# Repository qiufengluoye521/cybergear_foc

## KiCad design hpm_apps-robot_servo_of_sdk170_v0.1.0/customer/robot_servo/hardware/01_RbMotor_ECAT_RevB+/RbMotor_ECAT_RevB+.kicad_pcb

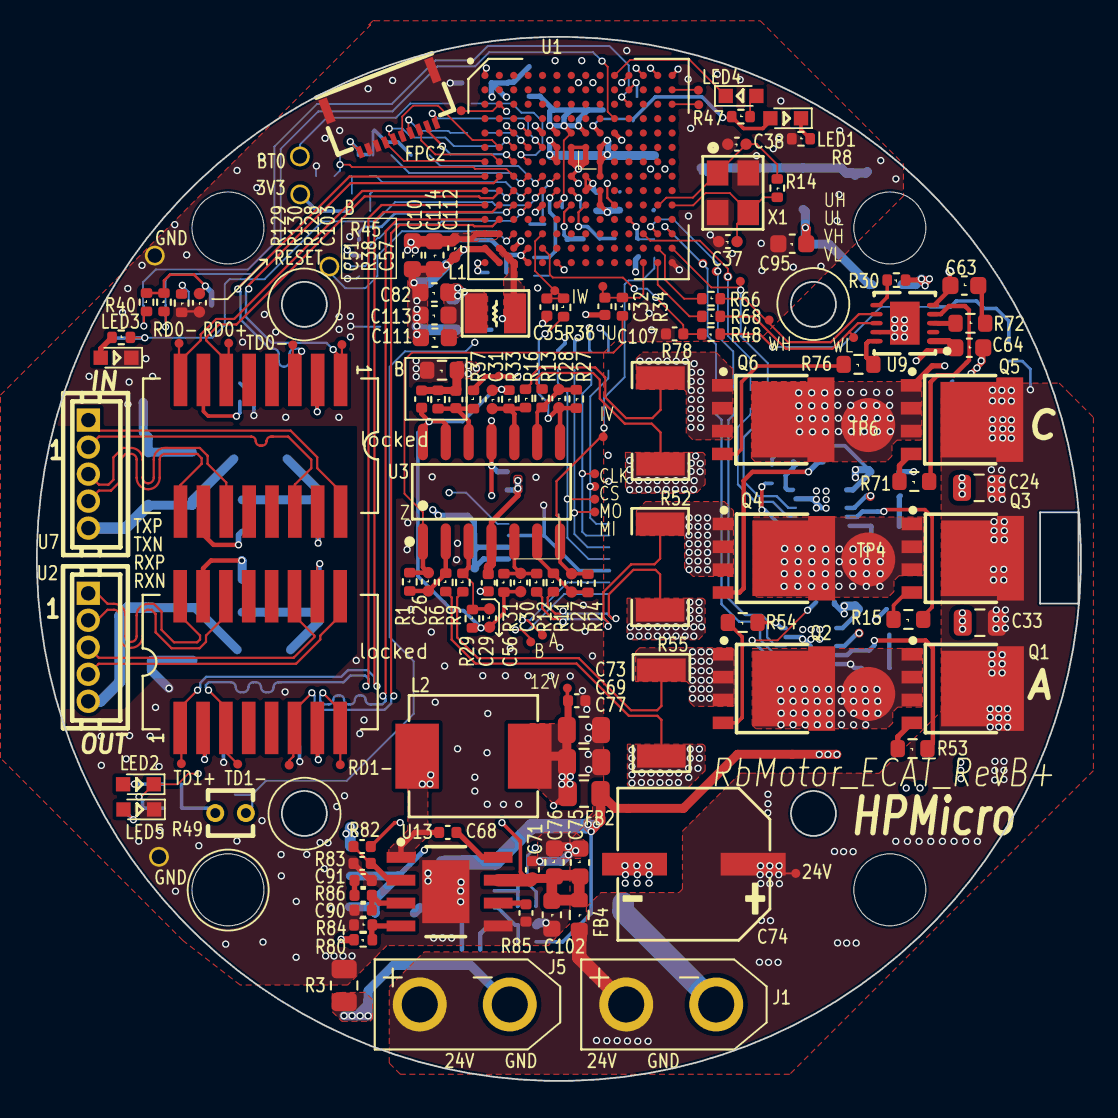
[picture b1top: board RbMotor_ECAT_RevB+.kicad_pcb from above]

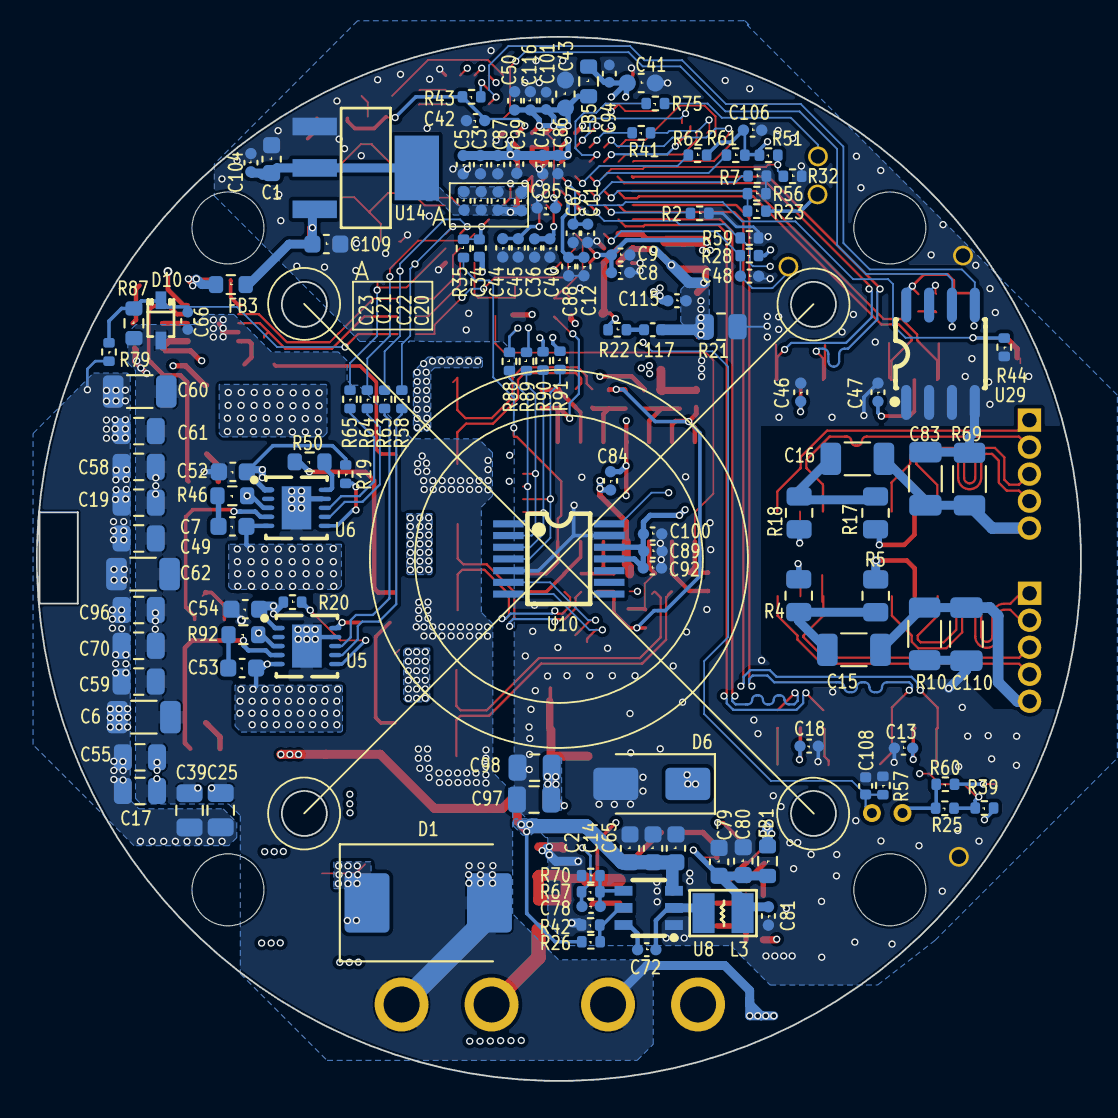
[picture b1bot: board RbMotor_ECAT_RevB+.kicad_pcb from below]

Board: 4 copper layers, 58.0 x 58.0 mm, 285 parts (137 on the bottom side), 158 nets.

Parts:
C1, C10, C79, C80, C82, C111, C113, C114: 22uF,10V; C_0603_1608Metric
C2, C65, C95: 10uF,25V; C_0603_1608Metric
C3, C4, C8, C11, C12, C22, C23, C40, C42, C45, C48, C50, C72, C81, C85, C89, C99, C103, C104, C106, C112, C115, C116: 0.1uF,16V; C_0402
C5, C9, C67, C84, C86, C87, C88, C92, C100: 10uF,10V; C_0402
C6, C15, C16, C60, C62, C83, C110: 1nF,2kV; C_1206_3216Metric
C7, C53, C63: 1uF,16V; C_0603_1608Metric
C13, C18, C46, C47: 10nF,50V; C_0402
C14, C52, C54, C64, C109: 0.1uF,50V; C_0603_1608Metric
C17, C19, C24, C25, C33, C39, C49, C55, C58, C59, C61, C70, C96: 10uF,35V; C_0805_2012Metric
C20, C21, C36, C44: 4.7uF,10V; C_0402
C26, C27, C28, C29, C30, C31, C78: 27pF,50V; C_0402
C32, C34, C35, C108: 0.01uF,16V; C_0402_1005Metric
C37, C38: 12pF,50V; C_0402
C41, C43: 10uF,10V; C_0603_1608Metric
C51, C56, C57, C68, C71, C73: 0.1uF,50V; C_0402_1005Metric
C66, C91: 1nF,50V; C_0402_1005Metric
C69, C77, C97, C98: 22uF,25V; C_0805_2012Metric
C74: 220uF,35V; CAP-SMD_BD8.0-L8.3-W8.3-LS9.1-FD
C75, C76, C102: 10uF,35V; C_0603_1608Metric
C90: 47pF,50V; C_0402_1005Metric
C94, C101, C107: 10nF,50V; C_0402_1005Metric
C117: 2.2nF,50V; C_0402_1005Metric
D1: SMCJ28A; D_SMC
D6: SS34A; D_SMA
D10: BZX384-C5V1; SOD-323
FB1, FB3: 600Ω@100MHz_1.3A; R_0603_1608Metric
FB2: 100Ω@100MHz_2A; R_0805_2012Metric
FB4, FB5: 100Ω@100MHz_2A; R_0603_1608Metric
FPC2: THD0510-10CL-GF; FPC_10P_0.5mm_JTAG
J1, J5: Conn_01x02; XT30U 母头插座
L1, L3: 4.7uH_1.4A; L252010
L2: 15uH，3A; IND-SMD_L7.0-W6.6_FXL0630
LED1, LED2, LED5: LED_GREEN; LED_0603
LED3, LED4: LED_RED; LED_0603
Q1, Q2, Q3, Q4, Q5, Q6: PSMN1R4-40YLD; sot_669_2
R1, R19, R20, R24, R27, R28, R29, R30, R31, R33, R37, R38, R42, R43, R57, R70, R84: 10K; R_0402_1005Metric
R2, R7: 2.49K; R_0402_1005Metric
R3: 0Ω; R_0805_2012Metric
R4, R5, R17, R18: 75Ω; R_0805_2012Metric
R6, R9, R11, R12, R13, R16: 1KΩ,0.1%; R_0402_1005Metric
R8, R47: 1K; R_0402_1005Metric
R10, R69: 1M; R_1206_3216Metric
R14: 1M; R_0402_1005Metric
R15, R50, R53, R54, R71, R76: 47Ω; R_0603_1608Metric
R21: 0Ω_0805; R_0805_2012Metric
R22, R34, R35, R36: 10Ω; R_0402_1005Metric
R23, R25, R32, R44, R51, R56, R59, R61, R62, R128, R129, R130: 4.7K; R_0402_1005Metric
R26: 24.9K; R_0402_1005Metric
R39, R40, R60: 330Ω; R_0402_1005Metric
R41: 100Ω; R_0402_1005Metric
R45: 0Ω; R_0603_1608Metric
R46, R72, R92: 2.2Ω; R_0603_1608Metric
R48, R58, R63, R64, R65, R66, R68, R88, R89, R90, R91: 33Ω; R_0402_1005Metric
R49: MF52A103F3950; RES-TH_L2.5-W2.5-P1.70-D0.3
R52, R55, R78: 1mΩ; R2010
R67: 45.3kΩ; R_0402_1005Metric
R75: 10K_0402; R_0402_1005Metric
R79: 200K; R_0402_1005Metric
R80: 140K; R_0402_1005Metric
R82, R86: 100K; C_0402_1005Metric
R83: 24.9K; C_0402_1005Metric
R85: 73.2K; C_0402_1005Metric
R87: 10K; R_0603_1608Metric
TP1, TP2, TP3, TP9, TP10, TP11, TP12, TP13, TP14, TP15, TP16, TP17, TP18, TP19, TP20, TP21, TP22, TP23, TP24, TP25, TP26, TP27, TP28, TP29, TP30, TP31, TP32, TP33, TP35, TP36, TP40: 0.5mm; TestPoint_Pad_D0.5mm
TP4, TP5, TP6: 0.5mm; SMD_3mm_Pad
TP7, TP8, TP37, TP38, TP39: 1.0mm; TestPoint_1.5
U1: HPM6E8YIGN1; BGA-196_14x14_12.0x12.0mm_P0.8mm
U2, U7: BX-ZH1.5-5P_ZZ; CONN-TH_ZH1.5-5A
U3: TP2274-SR; SOIC-14_L8.7-W3.9
U5, U6, U9: MP1907GQ–Z; QFN-10_L3.0-W3.0-P0.50-LS3.0-BL-EP
U8: TPS54302DDCR; SOT-23-6
U10: AS5047P-ATSM; TSSOP-14_L5.0-W4.4-P0.65-LS6.4-BL
U13: JW5116FESOP#TRPBF; SOIC-8EP
U14: LDL1117S33R; SOT-223-4_L6.5-W3.5-P2.30-LS7.0-BR
U29: AT24C02; SOIC-8
X1: 24MHz ±10ppm 12pF; 3225
locked: 网口变压器11FB-05NL; H1102_XFMR16_SM
locked#2: 网口变压器11FB-05NL; H1102_XFMR16_SM

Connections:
+1V2: C3.1, C4.1, C5.1, C82.1, C86.1, C87.1, C99.1, C111.1, C113.1, C115.1, L1.1, U1.F6 (VDD_SOC), U1.F9 (VDD_SOC), U1.G6 (VDD_SOC), U1.G9 (VDD_SOC), U1.H9 (VDD_SOC)
+3.3V: C8.2, C9.1, C10.1, C41.1, C42.1, C89.1, C92.1, C94.1, C100.1, C103.1, C106.1, C112.1, C114.1, FB1.1, FB5.2, FPC2.10, LED1.2 (A), R23.2, R25.2, R28.1, R43.2, R47.1, R49.2, R51.2, R60.2, R61.2, R62.2, R129.2, R130.2, TP8.1, U1.E9 (VPLLVUSB), U1.M1 (DCDC_IN), U1.M2 (DCDC_IN), U1.N4 (VBAT), U1.P4 (VPMC), U10.11 (VDD), U10.12 (VDD3V3), U29.8 (VCC)
+3.3VA: C1.1, C20.1, C21.1, C22.1, C23.1, C56.2, C84.2, C104.1, R37.2, TP36.1, U1.J9 (VANA), U1.K9 (VREFH), U3.4 (V+), U14.2 (VOUT), U14.4 (VOUT)
+12V: C2.1, C14.1, C52.1, C54.1, C64.1, C65.1, FB2.1, FB3.1, R19.1, R20.1, R26.2, R30.1, U5.1 (VDD), U6.1 (VDD), U8.3 (VIN), U9.1 (VDD)
+12VA: C69.1, C73.2, C77.1, C97.1, C98.1, FB2.2, L2.2, R80.2, TP1.1
+24V: C6.1, C17.1, C19.1, C24.1, C25.1, C33.1, C39.1, C49.1, C55.1, C58.1, C59.1, C60.1, C61.1, C62.1, C70.1, C74.1, C96.1, D1.1 (C), FB4.2, J1.2, J5.2, Q1.5 (D), Q3.5 (D), Q5.5 (D), R79.2, TP40.1
/ MAIN/03.MCU_PA_JTAG/JTAG_TCK: FPC2.4, R41.1
/ MAIN/03.MCU_PA_JTAG/JTAG_TDI: FPC2.6, U1.F3 (PA05/GPTMR1.COMP2/UART1.DE/UART1.RTS/SP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)
/ MAIN/03.MCU_PA_JTAG/JTAG_TDO: FPC2.5, U1.F2 (PA04/UART1.CTS/SPI1.SCLK/MCAN1.RXD/PWM0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)
/ MAIN/03.MCU_PA_JTAG/JTAG_TMS: FPC2.1, U1.F5 (PA07/GPTMR0.COMP0/UART1.TXD/I2C3.SCL/SP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)
/ MAIN/03.MCU_PA_JTAG/JTAG_TRST: FPC2.7, U1.G1 (PA08/GPTMR0.COMP1/UART2.TXD/I2C0.SCL/SP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)
/ MAIN/03.MCU_PA_JTAG/PA0: FPC2.3, U1.G2 (PA00/GPTMR1.COMP0/UART0.TXD/MCAN0.TXD/P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)
/ MAIN/03.MCU_PA_JTAG/PA1: FPC2.2, U1.G3 (PA01/GPTMR1.CAPT0/UART0.RXD/MCAN0.RXD/P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)
/ MAIN/03.MCU_PA_JTAG/PA2: R75.2, U1.G4 (PA02/GPTMR1.COMP1/UART0.DE/UART0.RTS/I2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)
/ MAIN/03.MCU_PA_JTAG/PA6: R41.2, U1.F4 (PA06/GPTMR0.CAPT0/UART1.RXD/I2C3.SDA/SP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)
/ MAIN/08.MCU_OSC/RESETN: C48.1, R28.2, TP38.1, U1.M3 (RSTN)
/ MAIN/08.MCU_OSC/VDD_PHY0CAP: C12.1, C88.1, U1.J6 (VDD_PHY0CAP)
/ MAIN/08.MCU_OSC/VDD_PHY1CAP: C11.1, C67.1, U1.H6 (VDD_PHY1CAP)
/ MAIN/09.ECAT_IN_OUT/RX0_N: U7.4, locked#2.9 (RX-)
/ MAIN/09.ECAT_IN_OUT/RX0_P: U7.3, locked#2.11 (RX+)
/ MAIN/09.ECAT_IN_OUT/RX1_N: U2.4, locked.9 (RX-)
/ MAIN/09.ECAT_IN_OUT/RX1_P: U2.3, locked.11 (RX+)
/ MAIN/09.ECAT_IN_OUT/TX0_N: U7.2, locked#2.14 (TX-)
/ MAIN/09.ECAT_IN_OUT/TX0_P: U7.1, locked#2.16 (TX+)
/ MAIN/09.ECAT_IN_OUT/TX1_N: U2.2, locked.14 (TX-)
/ MAIN/09.ECAT_IN_OUT/TX1_P: U2.1, locked.16 (TX+)
/ MAIN/10.AS5047 Encoder/CLK: R89.1, TP19.1, U10.2 (CLK)
/ MAIN/10.AS5047 Encoder/CSN: R88.1, TP18.1, U10.1 (CSn)
/ MAIN/10.AS5047 Encoder/MISO: R90.1, TP20.1, U10.3 (MISO)
/ MAIN/10.AS5047 Encoder/MOSI: R91.1, TP21.1, U10.4 (MOSI)
/ MAIN/12.Motor DriverA/MOTOR-U: C53.1, Q1.1 (S), Q1.2 (S), Q1.3 (S), Q2.5 (D), TP5.1, U5.5 (SW)
/ MAIN/13.Motor DriverB/MOTOR-V: C7.1, Q3.1 (S), Q3.2 (S), Q3.3 (S), Q4.5 (D), TP4.1, U6.5 (SW)
/ MAIN/14.Motor DriverC/MOTOR-W: C63.1, Q5.1 (S), Q5.2 (S), Q5.3 (S), Q6.5 (D), TP6.1, U9.5 (SW)
/ MAIN/PA16: TP25.1, U1.L1 (PA16/GPTMR3.COMP0/UART4.TXD/MCAN4.TXD/T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), locked.8 (RD-)
/ MAIN/PA17: TP24.1, U1.L2 (PA17/GPTMR3.CAPT0/UART4.RXD/MCAN4.RXD/T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), locked.6 (RD+)
/ MAIN/PA18: TP23.1, U1.K1 (PA18/GPTMR3.COMP1/UART4.DE/UART4.RTS/I2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), locked.3 (TD-)
/ MAIN/PA19: TP22.1, U1.K2 (PA19/GPTMR3.CAPT1/UART4.CTS/I2C6.SDA/SP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), locked.1 (TD+)
/ MAIN/PA20: TP29.1, U1.J1 (PA20/UART5.CTS/SPI2.SCLK/MCAN5.RXD/TSW0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), locked#2.8 (RD-)
/ MAIN/PA21: TP28.1, U1.J2 (PA21/GPTMR3.COMP2/UART5.DE/UART5.RTS/SP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), locked#2.6 (RD+)
/ MAIN/PA22: TP27.1, U1.H1 (PA22/GPTMR2.CAPT0/UART5.RXD/I2C7.SDA/SP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), locked#2.3 (TD-)
/ MAIN/PA23: TP26.1, U1.H2 (PA23/GPTMR2.COMP0/UART5.TXD/I2C7.SCL/SP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), locked#2.1 (TD+)
/ MAIN/PA24: R2.1, U1.K3 (PA24/GPTMR2.COMP1/UART6.TXD/I2C4.SCL/SP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)
/ MAIN/PA25: LED2.1 (K), R25.1, R39.2, R59.1, U1.K4 (PA25/GPTMR2.CAPT1/UART6.RXD/I2C4.SDA/SP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)
/ MAIN/PA26: R23.1, R56.1, U1.J3 (PA26/GPTMR2.COMP2/UART6.DE/UART6.RTS/SP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)
/ MAIN/PA27: R7.1, U1.J4 (PA27/UART6.CTS/SPI3.CS0/TSW0.P1_TXD2/ES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)
/ MAIN/PA28: R40.2, R44.1, U1.J5 (PA28/UART7.CTS/I2C5.SDA/SPI3.MISO/TSW0.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)
/ MAIN/PA29: R32.1, R51.1, U1.H3 (PA29/GPTMR3.COMP3/UART7.DE/UART7.RTS/I2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)
/ MAIN/PA30: R61.1, U1.H4 (PA30/UART7.RXD/SPI3.DAT2/MCAN7.RXD/TSW0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)
/ MAIN/PA31: R62.1, U1.H5 (PA31/GPTMR2.COMP3/UART7.TXD/SPI3.DAT3/M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)
/ MAIN/PB5: TP32.1, U1.C2 (PB05/GPTMR5.COMP2/UART9.DE/UART9.RTS/SP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), U10.14 (I)
/ MAIN/PB6: TP31.1, U1.E3 (PB06/GPTMR4.CAPT0/UART9.RXD/I2C3.SDA/SP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), U10.7 (A)
/ MAIN/PB7: TP30.1, U1.E4 (PB07/GPTMR4.COMP0/UART9.TXD/I2C3.SCL/SP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), U10.6 (B)
/ MAIN/PC18: LED4.1 (K), U1.A10 (PC18/GPTMR3.COMP1/UART4.DE/UART4.RTS/I2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)
/ MAIN/PC20: R89.2, U1.A11 (PC20/UART5.CTS/SPI3.SCLK/MCAN5.RXD/ESC0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)
/ MAIN/PC21: R43.1, R88.2, U1.B11 (PC21/GPTMR3.COMP2/UART5.DE/UART5.RTS/SP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)
/ MAIN/PC22: R90.2, U1.A12 (PC22/GPTMR2.CAPT0/UART5.RXD/I2C7.SDA/SP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)
/ MAIN/PC23: R91.2, U1.A13 (PC23/GPTMR2.COMP0/UART5.TXD/I2C7.SCL/SP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)
/ MAIN/PC24: TP33.1, U1.B14 (PC24/GPTMR2.COMP1/UART6.TXD/I2C4.SCL/SP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)
/ MAIN/PC25: TP35.1, U1.C14 (PC25/GPTMR2.CAPT1/UART6.RXD/I2C4.SDA/SP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)
/ MAIN/PD2: R130.1, U1.D10 (PD02/GPTMR5.COMP1/UART8.DE/UART8.RTS/I2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), U29.6 (SCL)
/ MAIN/PD3: R129.1, U1.C11 (PD03/GPTMR5.CAPT1/UART8.CTS/I2C2.SDA/SP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), U29.5 (SDA)
/ MAIN/PE0: R58.1, TP12.1, U1.M14 (PE00/GPTMR1.COMP0/UART0.TXD/MCAN0.TXD/T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)
/ MAIN/PE1: R63.1, TP13.1, U1.M13 (PE01/GPTMR1.CAPT0/UART0.RXD/MCAN0.RXD/D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)
/ MAIN/PE2: R64.1, TP2.1, U1.M12 (PE02/GPTMR1.COMP1/UART0.DE/UART0.RTS/I2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)
/ MAIN/PE3: R65.1, TP9.1, U1.N14 (PE03/GPTMR1.CAPT1/UART0.CTS/I2C2.SDA/SP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)
/ MAIN/PE4: R66.1, U1.N13 (PE04/UART1.CTS/SPI1.SCLK/MCAN1.RXD/DAO.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)
/ MAIN/PE5: R68.1, U1.P13 (PE05/GPTMR1.COMP2/UART1.DE/UART1.RTS/SP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)
/ MAIN/PF6: C32.1, R34.2, TP3.1, U1.P12 (PF06/GPTMR4.CAPT0/UART9.RXD/I2C3.SDA/SP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)
/ MAIN/PF8: C34.1, R35.2, U1.L11 (PF08/GPTMR4.COMP1/UART10.TXD/I2C0.SCL/S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)
/ MAIN/PF19: C35.1, R36.2, TP15.1, U1.M5 (PF19/GPTMR7.CAPT1/UART12.CTS/I2C6.SDA/S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)
/ MAIN/PF26: C108.1, R49.1, R57.2, U1.P6 (PF26/GPTMR6.COMP2/UART14.DE/UART14.RTS/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)
/ MAIN/PF31: C107.1, R48.2, U1.N5 (PF31/GPTMR6.COMP3/UART15.TXD/SPI7.DAT3/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)
AGND: C20.2, C21.2, C22.2, C23.2, C32.2, C34.2, C35.2, C51.2, C56.1, C57.2, C84.1, R38.1, R45.1, U1.H8 (VSSA), U1.J8 (VREFL), U3.11 (V-)
BGND: C6.2, C17.2, C19.2, C24.2, C25.2, C33.2, C39.2, C49.2, C52.2, C54.2, C55.2, C58.2, C59.2, C60.2, C61.2, C62.2, C64.2, C66.2, C70.2, C74.2, C96.2, D1.2 (A), D10.2 (A), J1.1, J5.1, R3.1, R6.1, R11.1, R13.1, R52.1, R55.1, R78.1, R87.1, U5.9 (VSS), U5.11 (EPAD), U6.9 (VSS), U6.11 (EPAD), U9.9 (VSS), U9.11 (EPAD)
DCDC_GND: C10.2, C82.2, C111.2, C112.2, C113.2, C114.2, C115.2, C117.2, R21.2, U1.N1 (DCDC_GND), U1.P2 (DCDC_GND)
DCDC_LP: L1.2, R22.1, U1.N2 (DCDC_LP), U1.P3 (DCDC_LP)
Earth: C16.2, C83.1, R69.1, U7.5
GND: C1.2, C2.2, C3.2, C4.2, C5.2, C8.1, C9.2, C11.2, C12.2, C13.1, C14.2, C18.1, C36.2, C37.2, C38.2, C40.2, C41.2, C42.2, C43.2, C44.2, C45.2, C46.1, C47.1, C48.2, C50.2, C65.2, C67.2, C69.2, C71.1, C73.1, C75.2, C76.2, C77.2, C79.2, C80.2, C81.2, C83.2, C85.2, C86.2, C87.2, C88.2, C89.2, C90.2, C91.2, C92.2, C94.2, C95.2, C97.2, C98.2, C99.2, C100.2, C101.2, C102.2, C103.2, C104.2, C106.2, C107.2, C108.2, C109.2, C110.2, C116.2, D6.2 (A), FPC2.8, FPC2.9, FPC2.11, FPC2.12, LED3.1 (K), LED5.1 (K), R2.2, R3.2, R7.2, R8.1, R10.2, R21.1, R32.2, R42.2, R44.2, R45.2, R56.2, R57.1, R59.2, R69.2, R70.1, R83.1, R84.1, R85.1, R128.2, TP37.1, TP39.1, U1.A1 (VSS), U1.A14 (VSS), U1.E5 (VSS), U1.E10 (VSS), U1.F7 (VSS), U1.F8 (VSS), U1.G7 (VSS), U1.G8 (VSS), U1.H7 (VSS), U1.J7 (VSS), U1.K5 (VSS), U1.K10 (VSS), U1.N3 (VSS), U1.P1 (VSS), U1.P14 (VSS), U8.1 (GND), U10.5 (Test), U10.13 (GND), U13.5 (GND), U13.9 (EP), U14.1 (GND), U29.1 (E0), U29.2 (E1), U29.3 (E2), U29.4 (VSS), X1.2 (GND), X1.4 (GND)
MT_IU: Q2.1 (S), Q2.2 (S), Q2.3 (S), R9.1, R55.2
MT_IV: Q4.1 (S), Q4.2 (S), Q4.3 (S), R12.1, R52.2
MT_IW: Q6.1 (S), Q6.2 (S), Q6.3 (S), R16.1, R78.2
unnamed: C7.2, R46.2
unnamed: C13.2, locked.2 (CT)
unnamed: C15.1, R4.1, R5.1
unnamed: C16.1, R17.1, R18.1
unnamed: C18.2, locked.7 (CT)
unnamed: C26.1, R1.1, R6.2, U3.2
unnamed: C26.2, R1.2, R34.1, U3.1
unnamed: C27.1, R11.2, R24.1, U3.6
unnamed: C27.2, R24.2, R35.1, TP14.1, U3.7
unnamed: C28.1, R13.2, R27.1, U3.9
unnamed: C28.2, R27.2, R36.1, U3.8
unnamed: C29.1, C30.1, C31.1, C51.1, R29.1, R31.1, R33.1, U3.13, U3.14
unnamed: C29.2, R9.2, R29.2, U3.3
unnamed: C30.2, R12.2, R31.2, U3.5
unnamed: C31.2, R16.2, R33.2, U3.10
unnamed: C46.2, locked#2.2 (CT)
unnamed: C47.2, locked#2.7 (CT)
unnamed: C53.2, R92.2
unnamed: C57.1, R37.1, R38.2, U3.12
unnamed: C63.2, R72.2
unnamed: C78.2, C79.1, C80.1, C81.1, FB1.2, L3.2, R67.2
unnamed: C91.1, R86.1
unnamed: C43.1, C50.1, C85.1, C101.1, C116.1, FB5.1, U1.E6 (VIO_B01), U1.E7 (VIO_B01), U1.E8 (VIO_B01), U1.K6 (VIO_B01)
unnamed: C117.1, R22.2
unnamed: C68.2, D6.1 (K), L2.1, U13.1 (SW)
unnamed: C66.1, D10.1 (C), R48.1, R79.1, R87.2
unnamed: LED1.1 (K), R8.2
unnamed: LED2.2 (A), R60.1
unnamed: LED3.2 (A), R40.1
unnamed: LED4.2 (A), R47.2
unnamed: LED5.2 (A), R39.1
unnamed: Q1.4 (G), R53.2
unnamed: Q2.4 (G), R54.2
unnamed: Q3.4 (G), R15.2
unnamed: Q4.4 (G), R50.2
unnamed: Q5.4 (G), R71.2
unnamed: Q6.4 (G), R76.2
unnamed: R4.2, locked.10 (CT)
unnamed: R5.2, locked.15 (CT)
unnamed: R17.2, locked#2.10 (CT)
unnamed: R18.2, locked#2.15 (CT)
unnamed: R75.1, TP7.1
unnamed: C37.1, R14.2, U1.K14 (XTALI), X1.3 (X2)
unnamed: C38.1, R14.1, U1.K13 (XTALO), X1.1 (X1)
unnamed: R92.1, TP17.1, U5.3 (BST)
unnamed: R53.1, U5.4 (DRVH)
unnamed: R54.1, U5.10 (DRVL)
unnamed: R20.2, U5.6 (EN)
unnamed: R58.2, U5.7 (INH)
unnamed: R63.2, U5.8 (INL)
unnamed: R46.1, TP16.1, U6.3 (BST)
unnamed: R15.1, U6.4 (DRVH)
unnamed: R50.1, U6.10 (DRVL)
unnamed: R19.2, U6.6 (EN)
unnamed: R64.2, U6.7 (INH)
unnamed: R65.2, U6.8 (INL)
unnamed: R26.1, R42.1, U8.5 (EN)
unnamed: C72.2, L3.1, U8.2 (SW)
unnamed: C72.1, U8.6 (VBST)
unnamed: C78.1, R67.1, R70.2, U8.4 (VFB)
unnamed: R72.1, U9.3 (BST)
unnamed: R71.1, U9.4 (DRVH)
unnamed: R76.1, U9.10 (DRVL)
unnamed: R30.2, U9.6 (EN)
unnamed: R66.2, TP10.1, U9.7 (INH)
unnamed: R68.2, TP11.1, U9.8 (INL)
unnamed: C68.1, U13.8 (BST)
unnamed: C90.1, R86.2, U13.3 (COMP)
unnamed: R82.1, R83.2, U13.2 (EN)
unnamed: R80.1, R84.2, U13.4 (FB)
unnamed: R85.2, U13.6 (RT)
unnamed: C71.2, C75.1, C76.1, C102.1, FB4.1, R82.2, U13.7 (VIN)
unnamed: C95.1, C109.1, FB3.2, U14.3 (VIN)
unnamed: R128.1, U29.7 (~WC)
PE: C15.2, C110.1, R10.1, U2.5
VDD_OTPCAP: C36.1, C40.1, U1.K7 (VDD_OTPCAP)
VDD_PMCCAP: C44.1, C45.1, U1.K8 (VDD_PMCCAP)

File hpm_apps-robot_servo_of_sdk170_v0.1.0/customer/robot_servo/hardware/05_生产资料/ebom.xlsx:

RbMotor_ECAT_RevB+ BOM
null | References | Value | Footprint | ASSY_OPT | Company | Model | Quantity
1 | C3, C4, C8, C11, C12, C22, C23, C40, C42, C45, C48, C50, C72, C81, C85, C89, C9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 | 0.1uF,16V | C_0402 |  | SAMSUNG(三星) | CL05B104KO5NNNC | 23
2 | C17, C19, C24, C25, C33, C39, C49, C55, C58, C59, C61, C70, C96 | 10uF,35V | C_0805_2012Metric |  | muRata(村田) | GRM21BR6YA106KE43L | 13
3 | C1, C10, C79, C80, C82, C111, C113, C114 | 22uF,10V | C_0603_1608Metric |  | SAMSUNG(三星) | CL10A226MP8NUNE | 8
4 | C5, C9, C84, C86, C87, C92, C100，C67, C88 | 10uF,10V | C_0402 |  | SAMSUNG(三星) | CL05A106MP5NUNC | 9
5 | C26, C27, C28, C29, C30, C31, C78 | 27pF,50V | C_0402 |  | FH(风华) | 0402CG270J500NT | 7
6 | C20, C21, C36, C44, | 4.7uF,10V | C_0402 |  | SAMSUNG(三星) | CL05A475MP5NRNC | 4
7 | C14, C52, C54, C64, C109 | 0.1uF,50V | C_0603_1608Metric |  | YAGEO | CC0603JRX7R9BB104 | 5
8 | C13, C18, C46, C47 | 10nF,50V | C_0402 |  | SAMSUNG(三星) | CL05B103KB5NNNC | 4
9 | C15, C16, C83, C110 | 1nF,2kV | C_1206_3216Metric |  | YAGEO(国巨) | CC1206KKX7RDBB102 | 4
10 | C32, C34, C35, C108 | 0.01uF,16V | C_0402_1005Metric |  | YAGEO(国巨) | CC0402KRX7R7BB103 | 4
11 | C69, C77, C97, C98 | 22uF,25V | C_0805_2012Metric |  | SAMSUNG(三星) | CL21A226MAQNNNE | 4
12 | C2, C65, C95 | 10uF,25V | C_0603_1608Metric |  | SAMSUNG(三星) | CL10A106MA8NRNC | 3
13 | C6, C60, C62 | 1nF,2kV | C_1206_3216Metric |  | FH(风华) | 1206B102K202NT | 3
14 | C7, C53, C63 | 1uF,16V | C_0603_1608Metric |  | SAMSUNG(三星) | CL10A105KO8NNNC | 3
15 | C51, C56, C57 | 0.1uF,50V | C_0402_1005Metric |  | SAMSUNG(三星) | 0402B104K500NT | 3
16 | C68, C71, C73 | 0.1uF,50V | C_0402_1005Metric |  | YAGEO | CC0402KRX7R9BB104 | 3
17 | C75, C76, C102 | 10uF,35V | C_0603_1608Metric |  | muRata(村田) | GRM188R6YA106MA73D | 3
18 | C94, C101, C107 | 10nF,50V | C_0402_1005Metric |  | SAMSUNG(三星) | CL05B103KB5NNNC | 3
19 | C37, C38 | 12pF,50V | C_0402 |  | YAGEO(国巨) | CC0402JRNPO9BN120 | 2
20 | C41, C43 | 10uF,10V | R_0603_1608Metric |  | SAMSUNG(三星) | CL10A106KP8NNNC | 2
21 | C66 | 1nF,50V | C_0402 |  | YAGEO |  | 1
22 | C74 | 220uF,35V | CAP-SMD_BD8.0-L8.3-W8.3-LS9.1-FD |  | DMBJ(振宝佳) | JBLM2221M035D090RTM | 1
23 | C90 | 47pF,50V | C_0402_1005Metric |  | YAGEO(国巨) | CC0402JRNPO9BN470 | 1
24 | C91 | 1nF,50V | C_0402_1005Metric |  | YAGEO | CC0402KRX7R9BB102 | 1
25 | C117 | 2.2nF,50V | C_0402_1005Metric |  | SAMSUNG(三星) | CL05B222KB5NNNC | 1
26 | R1, R19, R20, R24, R27, R28, R29, R30, R31, R33, R37, R38, R42, R43, R57, R70, 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 | 10K | R_0402_1005Metric |  | UNI-ROYAL(厚声) | 0402WGF1002TCE | 17
27 | R48, R58, R63, R64, R65, R66, R68, R88, R89, R90, R91 | 33Ω | R_0402_1005Metric |  | UNI-ROYAL(厚声) | 0402WGF330JTCE | 11
28 | R25, R44, R51, R56, R61, R62, R128, R129, R130 | 4.7K | R_0402_1005Metric |  | UNI-ROYAL(厚声) | 0402WGF4701TCE | 9
29 | R6, R9, R11, R12, R13, R16 | 1KΩ,0.1% | R_0402_1005Metric |  | UNI-ROYAL(厚声) |  | 6
30 | R15, R50, R53, R54, R71, R76 | 47Ω | R_0603_1608Metric |  | UNI-ROYAL(厚声) | 0603WAF470JT5E | 6
31 | R4, R5, R17, R18 | 75Ω | R_0805_2012Metric |  | UNI-ROYAL(厚声) | 0805W8F750JT5E | 4
32 | R22, R34, R35, R36 | 10Ω | R_0402_1005Metric |  | UNI-ROYAL(厚声) | 0402WGF100JTCE | 4
33 | R23, R32, R59 | 4.7K | R_0402_1005Metric | DNP | UNI-ROYAL(厚声) | 0402WGF4701TCE | 3
34 | R46, R72, R92 | 2.2Ω | R_0603_1608Metric |  | UNI-ROYAL(厚声) | 0603WAF220KT5E | 3
35 | R52, R55, R78 | 1mΩ | R2010 |  | Milliohm(毫欧) | HoLR2010-1W-1mR-1% | 3
36 | R2, R7 | 2.49K | R_0402_1005Metric |  | FH(风华) | RC-02W2491FT | 2
37 | R10, R69 | 1M | R_1206_3216Metric |  | Viking(光颉) | ARG06BTC1004 | 2
38 | R40, R60 | 330Ω | R_0402_1005Metric |  | UNI-ROYAL(厚声) | 0402WGF3300TCE | 2
39 | R82, R86 | 100K | C_0402_1005Metric |  | UNI-ROYAL(厚声) | 0402WGF1003TCE | 2
40 | R3 | 0Ω | R_0805_2012Metric |  | FH(风华) | RS-05000JT | 1
41 | R8 | 1K | R_0402_1005Metric |  | UNI-ROYAL(厚声) | 0402WGF1001TCE | 1
42 | R14 | 1M | R_0402_1005Metric |  | UNI-ROYAL(厚声) | CQ02WGJ0105TCE | 1
43 | R21 | 0Ω_0805 | R_0805_2012Metric |  | FH(风华) | RS-05000JT | 1
44 | R26 | 24.9K | R_0402_1005Metric |  | UNI-ROYAL(厚声) |  | 1
45 | R39 | 330Ω | R_0402_1005Metric | DNP | UNI-ROYAL(厚声) | 0402WGF3300TCE | 1
46 | R41 | 100Ω | R_0402_1005Metric |  | UNI-ROYAL(厚声) | 0402WGF1000TCE | 1
47 | R45 | 0Ω | R_0603_1608Metric |  | UNI-ROYAL(厚声) | 0603WAF0000T5E | 1
48 | R47 | 1KΩ | R_0402_1005Metric |  | UNI-ROYAL(厚声) | 0402WGF1001TCE | 1
49 | R49 | MF52A103F3950 | RES-TH_L2.5-W2.5-P1.70-D0.3 |  | SURGING(绍鑫) | MF52A103F3950 | 1
50 | R67 | 45.3kΩ | R_0402_1005Metric |  | UNI-ROYAL(厚声) | 0402WGF4532TCE | 1
51 | R75 | 10K_0402 | R_0402_1005Metric |  | UNI-ROYAL(厚声) | 0402WGF1002TCE | 1
52 | R79 | 200K | R_0402_1005Metric |  | UNI-ROYAL(厚声) | 0402WGF2003TCE | 1
53 | R80 | 140K | R_0402_1005Metric |  | UNI-ROYAL(厚声) | 0402WGF1403TCE | 1
54 | R83 | 24.9K | C_0402_1005Metric |  | UNI-ROYAL(厚声) | 0603WAF2492T5E | 1
55 | R85 | 73.2K | C_0402_1005Metric |  | UNI-ROYAL(厚声) | 0402WGF7322TCE | 1
56 | R87 | 10K | R_0603_1608Metric |  | YAGEO |  | 1
57 | L1, L3 | 4.7uH_1.4A | L252010 |  | muRata(村田) | DFE252010F-4R7M | 2
58 | L2 | 15uH，3A | IND-SMD_L7.0-W6.6_FXL0630 |  | cjiang(长江微电) | FXL0630-150-M | 1
59 | D1 | SMCJ28A | D_SMC |  | Littelfuse(美国力特) | SMCJ28A | 1
60 | D6 | SS34A | D_SMA |  | YANGJIE(扬杰) | SS34A | 1
61 | D10 | BZX384-C5V1 | SOD-323 |  | Nexperia(安世) | BZX384-C5V1 | 1
62 | U5, U6, U9 | MP1907GQ–Z | QFN-10_L3.0-W3.0-P0.50-LS3.0-BL-EP |  |  | MP1907GQ–Z | 3
63 | U2, U7 | BX-ZH1.5-5P_ZZ | CONN-TH_ZH1.5-5A |  | Bossie(博锡) | BX-ZH1.5-5PZZ | 2
64 | U1 | HPM6E8YIGN1 | BGA-196_14x14_12.0x12.0mm_P0.8mm |  |  | HPM6E8YIGN1 | 1
65 | U3 | TP2274-SR | SOIC-14_L8.7-W3.9 |  | 3PEAK(思瑞浦) | TP2274-SR | 1
66 | U8 | TPS54302DDCR | SOT-23-6 |  | TI | TPS54302DDCR | 1
67 | U10 | AS5047P-ATSM | TSSOP-14_L5.0-W4.4-P0.65-LS6.4-BL |  | ams(艾迈斯半导体) | AS5047P-ATSM | 1
68 | U13 | JW5116FESOP#TRPBF | SOIC-8EP |  | Joulwatt(杰华特) | JW5116FESOP#TRPBF | 1
69 | U14 | LDL1117S33R | SOT-223-4_L6.5-W3.5-P2.30-LS7.0-BR |  | ST(意法半导体) | LDL1117S33R | 1
70 | U29 | AT24C02 | SOIC-8 |  | IDCHIP(英锐芯) | AT24C02 | 1
71 | X1 | 24MHz ±10ppm 12pF | 3225 |  | EPSON(爱普生) | X1E0000210129 | 1
73 | Q1, Q2, Q3, Q4, Q5, Q6 | PSMN1R4-40YLD | sot_669_2 |  | Nexperia(安世) | PSMN1R4-40YLD | 6
75 | LED1, LED2, LED5 | LED_GREEN | LED_0603 |  | 国星光电 | NCD0603C1 | 3
77 | FB1, FB3 | 600Ω@100MHz_1.3A | R_0603_1608Metric |  | muRata(村田) | BLM18KG601SN1D | 2
78 | FB4, FB5 | 100Ω@100MHz_2A | R_0603_1608Metric |  | Sunlord(顺络) | PZ1608D101-2R0TF | 2
79 | LED3, LED4 | LED_RED | LED_0603 |  | 国星光电 | NCD0603R1 | 2
80 | T1, T2 | 网口变压器11FB-05NL | H1102_XFMR16_SM |  | YDS(元册科技) | 11FB-05NL | 2
81 | FB2 | 100Ω@100MHz_2A | R_0805_2012Metric |  | Sunlord(顺络) | PZ2012U101-2R0TF | 1
82 | FPC2 | THD0510-10CL-GF | FPC_10P_0.5mm_JTAG |  | THD(台华达) | THD0510-10CL-GF | 1
83 | J1, J5 | Conn_01x02 | XT30U 母头插座 |  |  | XT30UPB-M 公头 PCB焊板 | 2

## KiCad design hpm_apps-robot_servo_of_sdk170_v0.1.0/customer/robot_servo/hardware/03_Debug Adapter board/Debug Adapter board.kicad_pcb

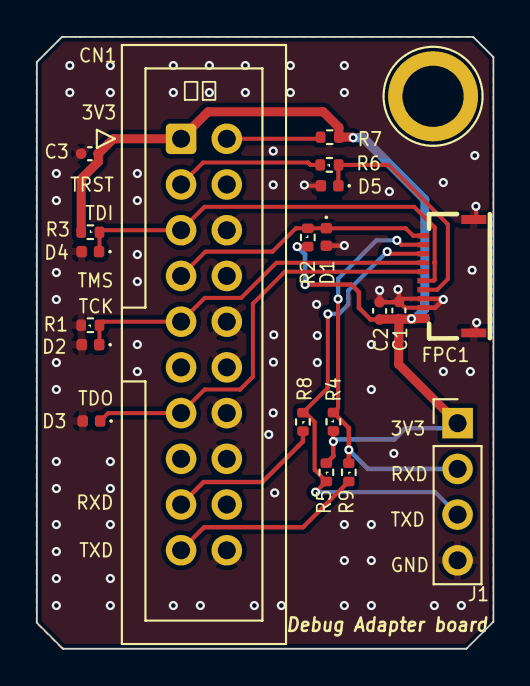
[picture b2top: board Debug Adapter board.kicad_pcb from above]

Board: 2 copper layers, 25.4 x 34.0 mm, 21 parts (0 on the bottom side), 13 nets.

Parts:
C1, C3: 0.1uF,16V; C_0402_1005Metric
C2: 10uF,10V; C_0402_1005Metric
CN1: 2.54-2*10P简牛-2; IDC-Header_2x10_P2.54mm
D1, D2, D3, D4, D5: LXES1UTAA1-157; D_0402_1005Metric
FPC1: FPC_10P_0.5MM_下接; FPC-SMD_10P_0.5mm_2
J1: Conn_01x04; PinHeader_1x04_P2.54mm_Vertical
R1, R2, R3, R4, R5: 10K; R_0402_1005Metric
R6, R8, R9: 0Ω; R_0402_1005Metric
R7: NC; R_0402_1005Metric
TP2: TestPoint; TestPoint_Plated_Hole_D4.0mm

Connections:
3.3V_Main: C1.1, C2.1, C3.1, CN1.1 (VREF), FPC1.1, J1.1, R2.1, R3.1, R4.1, R5.1, R7.2
/PY0/JTAG_TDO: CN1.13 (TDO), D3.1 (A), FPC1.6
/PY1/JTAG_TDI: CN1.5 (TDI), D4.1 (A), FPC1.5, R3.2
/PY2/JTAG_TCK: CN1.9 (TCK), D2.1 (A), FPC1.7, R1.1
/PY3/JTAG_TMS: CN1.7 (TMS), D1.1 (A), FPC1.10, R2.2
/PY4/JTAG_TRST: D5.1 (A), FPC1.4, R6.1
/PY6/UART0_TXD: FPC1.8, J1.3, R5.2, R8.1
/PY7/UART0_RXD: FPC1.9, J1.2, R4.2, R9.1
GND: C1.2, C2.2, C3.2, CN1.4 (GND), CN1.6 (GND), CN1.8 (GND), CN1.10 (GND), CN1.12 (GND), CN1.14 (GND), CN1.16 (GND), CN1.18 (GND), CN1.20 (GND), D1.2 (K), D2.2 (K), D3.2 (K), D4.2 (K), D5.2 (K), FPC1.2, FPC1.3, FPC1.11, FPC1.12, J1.4, R1.2
unnamed: CN1.17 (NC), R8.2
unnamed: CN1.19 (NC), R9.2
unnamed: CN1.3 (TRST), R6.2
unnamed: CN1.2 (VCC), R7.1

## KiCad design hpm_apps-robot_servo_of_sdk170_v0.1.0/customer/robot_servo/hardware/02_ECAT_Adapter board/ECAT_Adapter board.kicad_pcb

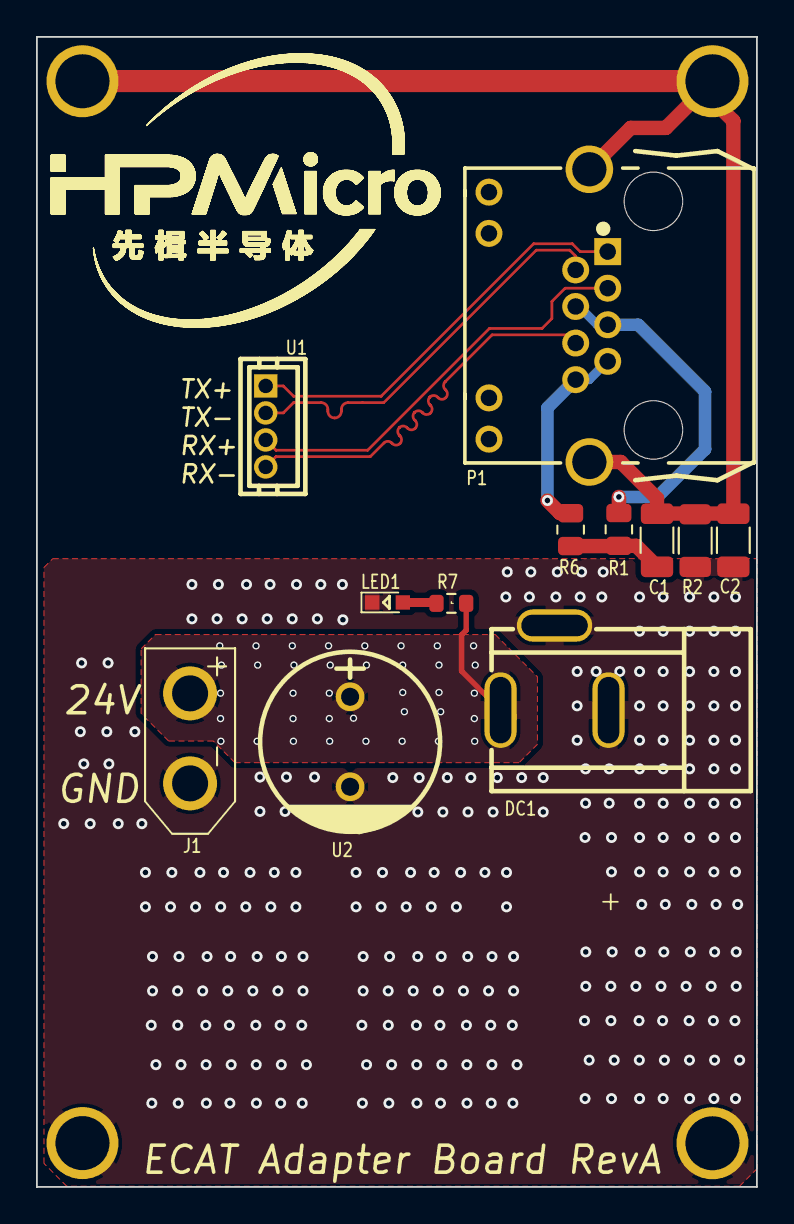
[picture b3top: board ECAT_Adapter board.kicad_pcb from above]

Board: 4 copper layers, 40.0 x 63.9 mm, 17 parts (0 on the bottom side), 11 nets.

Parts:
C1, C2: 1nF,2kV; C_1206_3216Metric
DC1: DC-005-2.5A-2.5; DC-005-2.5A-2.0
H1, H2, H3, H4: MountingHole_Pad; FIX-4mm
J1: Conn_01x02; XT30U 母头插座
LED1: LED_RED; LED_0603
MARK2: HPM Logo; HPM LOGO 8
P1: RJ45; RJ45-TH_B-1-1
R1, R6: 75Ω_0805; R_0805_2012Metric
R2: 1M; R_1206_3216Metric
R7: 10K; R_0603_1608Metric
U1: BX-ZH1.5-4PZZ; TH_ZH1.5-4P
U2: 470UF_50V; CAP-TH_BD10.0

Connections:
+24V: DC1.1, J1.2, R7.2, U2.1
/RX+: P1.3, U1.3
/RX-: P1.6, U1.4
/TX+: P1.1, U1.1
/TX-: P1.2, U1.2
Earth: C1.2, C2.1, H1.1, H2.1, P1.0 (S), R2.1
GND: C2.2, DC1.2, DC1.3, H3.1, H4.1, J1.1, LED1.1 (K), R2.2, U2.2
unnamed: C1.1, R1.1, R6.1
unnamed: LED1.2 (A), R7.1
unnamed: P1.4, P1.5, R1.2
unnamed: P1.7, P1.8, R6.2

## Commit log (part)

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2026-03-17 Add project title to README
2026-03-17 <init><add>增加初始化文件，来自网络
2026-03-25 <bug><修改>解决编译出现的问题，可以正常编译通过
2026-05-06 <bug><修改>解决boot编译出现的问题，可以正常编译通过
2026-06-27 <调试><debug>程序调试，可以正常运行
